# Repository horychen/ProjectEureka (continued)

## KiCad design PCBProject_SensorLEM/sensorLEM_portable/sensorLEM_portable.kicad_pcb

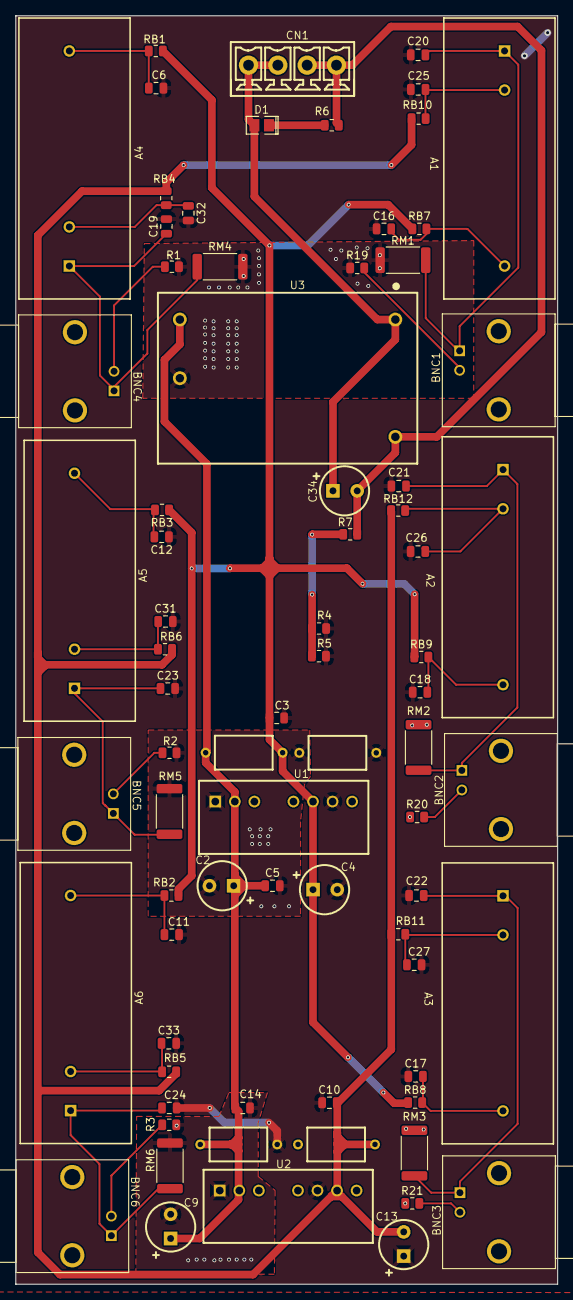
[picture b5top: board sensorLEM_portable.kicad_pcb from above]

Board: 2 copper layers, 70.4 x 164.8 mm, 76 parts (0 on the bottom side), 32 nets.

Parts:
A1, A2, A3, A4, A5, A6: LA55-P; LEM_LA 55-P
BNC1, BNC2, BNC3, BNC4, BNC5, BNC6: BNC; CPBNCPC010
C1, C7, C8, C15: 1nF; CAP-TH_L7.5-W4.5-P10.00-D0.6
C2, C4, C9, C13, C34: 100uf 25V 贴片铝电解; CAP_6.4mm
C3, C5, C10, C14: 105; C_0805_2012Metric
C6, C11, C12, C16, C17, C18, C25, C26, C27, C31, C32, C33: 47nf; C_0805_2012Metric
C19, C20, C21, C22, C23, C24: 4.7uF; C_0805_2012Metric
CN1: DB2EVC-3.81-4P-GN; CONN-TH_4P-P3.81_DB2EVC-3.81-4P
D1: LED0; LED0805
R1, R2, R3, R19, R20, R21: 0R; R_0805_2012Metric
R4, R5, R7: DNP; R_0805_2012Metric
R6: 4.7k; R_0805_2012Metric
RB1, RB2, RB3, RB4, RB5, RB6, RB7, RB8, RB9, RB10, RB11, RB12: 0R; R_0805_2012Metric
RM1, RM2, RM3, RM4, RM5, RM6: 24R 1%精度; R_2512_6332Metric
U1, U2: VRB1212S-6WR3; SIP,22x9.5mm
U3: FT-AX1D; PWRM-TH_MORNSUN_FT-AX1D

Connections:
12VGND: C3.2, C4.2, C6.1, C7.2, C8.2, C10.1, C11.1, C12.1, C13.1, C16.1, C17.1, C18.1, C19.2, C20.2, C21.2, C22.2, C23.2, C24.2, C25.2, C26.2, C27.2, C31.2, C32.2, C33.2, R4.2, R5.2, U1.7 (0V), U2.6 (VO+)
+12: C1.2, C3.1, C4.1, RB1.1, RB2.1, RB3.1, RB7.1, RB8.1, RB9.1, U1.6 (VO+)
-12: C10.2, C13.2, C15.2, RB4.2, RB5.2, RB6.2, RB10.2, RB11.2, RB12.2, U2.7 (0V)
/CSO1: A1.1 (M), BNC1.1 (X), C20.1, RM1.1
/CSO2: A2.1 (M), BNC2.1 (X), C21.1, RM2.1
/CSO3: A3.1 (M), BNC3.1 (X), C22.1, RM3.1
/CSO4: A4.1 (M), BNC4.1 (X), C19.1, RM4.1
/CSO5: A5.1 (M), BNC5.1 (X), C23.1, RM5.1
/CSO6: A6.1 (M), BNC6.1 (X), C24.1, RM6.1
A12V: C1.1, C2.1, C5.1, C8.1, C9.1, C14.1, U1.2 (VIN), U2.2 (VIN), U3.4 (-VO)
AGND: C2.2, C5.2, C7.1, C9.2, C14.2, C15.1, R1.1, R2.1, R3.1, R4.1, R5.1, R7.2, R19.1, R20.1, R21.1, RM1.2, RM2.2, RM3.2, RM4.2, RM5.2, RM6.2, U1.1 (GND), U2.1 (GND), U3.3 (+VO)
D12V1: C34.1, CN1.1, CN1.2, D1.1 (A), U3.1 (-VIN)
D12VGND: C34.2, CN1.3, CN1.4, R6.1, R7.1, U3.2 (+VIN)
unnamed: A1.2 (NEG), C25.1, RB10.1
unnamed: A1.3 (POS), C16.2, RB7.2
unnamed: A2.2 (NEG), C26.1, RB12.1
unnamed: A2.3 (POS), C18.2, RB9.2
unnamed: A3.2 (NEG), C27.1, RB11.1
unnamed: A3.3 (POS), C17.2, RB8.2
unnamed: A4.2 (NEG), C32.1, RB4.1
unnamed: A4.3 (POS), C6.2, RB1.2
unnamed: A5.2 (NEG), C31.1, RB6.1
unnamed: A5.3 (POS), C12.2, RB3.2
unnamed: A6.2 (NEG), C33.1, RB5.1
unnamed: A6.3 (POS), C11.2, RB2.2
unnamed: BNC1.2 (Y), R19.2
unnamed: BNC2.2 (Y), R20.2
unnamed: BNC3.2 (Y), R21.2
unnamed: BNC4.2 (Y), R1.2
unnamed: BNC5.2 (Y), R2.2
unnamed: BNC6.2 (Y), R3.2
unnamed: D1.2 (K), R6.2

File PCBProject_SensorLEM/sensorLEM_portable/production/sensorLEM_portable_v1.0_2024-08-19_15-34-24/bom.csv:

Designator,Footprint,Quantity,Value,LCSC Part #
"A1, A2, A3, A4, A5, A6",LEM_LA 55-P,6,LA55-P,
"BNC1, BNC2, BNC3, BNC4, BNC5, BNC6",CPBNCPC010,6,BNC,
"C1, C15, C7, C8",CAP-TH_L7.5-W4.5-P10.00-D0.6,4,1nF,
"C10, C14, C3, C5",0805,4,105,
"C11, C12, C16, C17, C18, C25, C26, C27, C31, C32, C33, C6",0805,12,47nf,
"C13, C2, C34, C4, C9",CAP_6.4mm,5,100uf 25V 贴片铝电解,
"C19, C20, C21, C22, C23, C24",0805,6,4.7uF,
CN1,CONN-TH_4P-P3.81_DB2EVC-3.81-4P,1,DB2EVC-3.81-4P-GN,
D1,LED0805,1,LED0,
"R1, R19, R2, R20, R21, R3, RB1, RB10, RB11, RB12, RB2, RB3, RB4, RB5, RB6, RB7, RB8, RB9",0805,18,0R,
R6,0805,1,4.7k,
"RM1, RM2, RM3, RM4, RM5, RM6",2512,6,24R 1%精度,
"U1, U2","SIP,22x9.5mm",2,VRB1212S-6WR3,
U3,PWRM-TH_MORNSUN_FT-AX1D,1,FT-AX1D,

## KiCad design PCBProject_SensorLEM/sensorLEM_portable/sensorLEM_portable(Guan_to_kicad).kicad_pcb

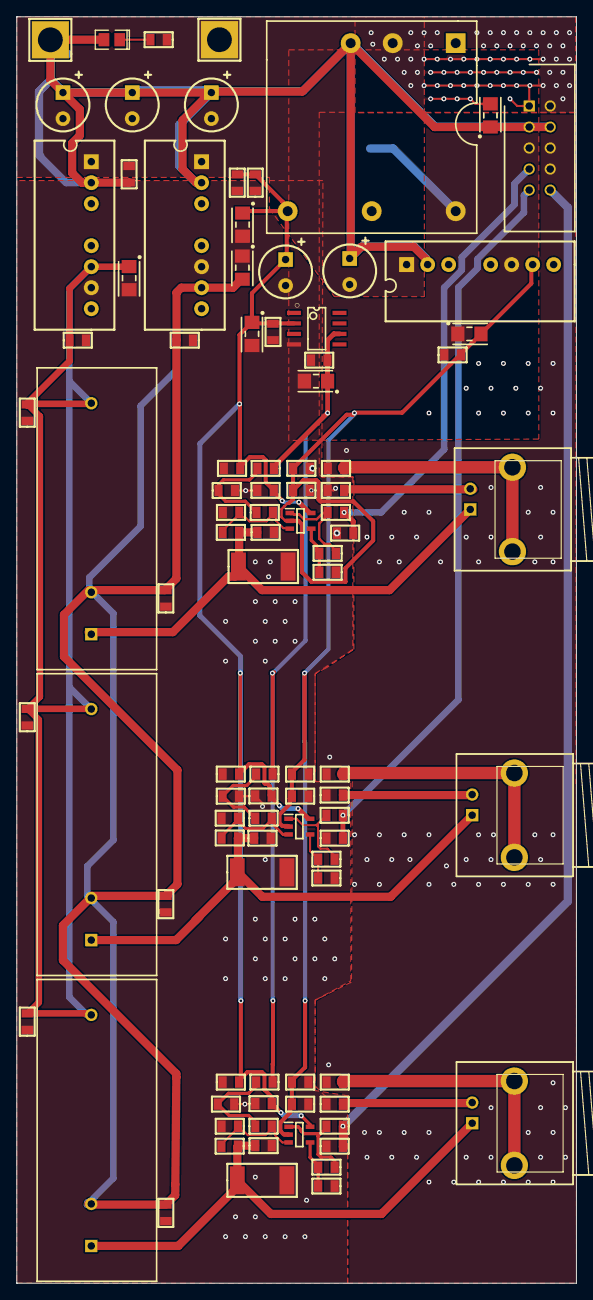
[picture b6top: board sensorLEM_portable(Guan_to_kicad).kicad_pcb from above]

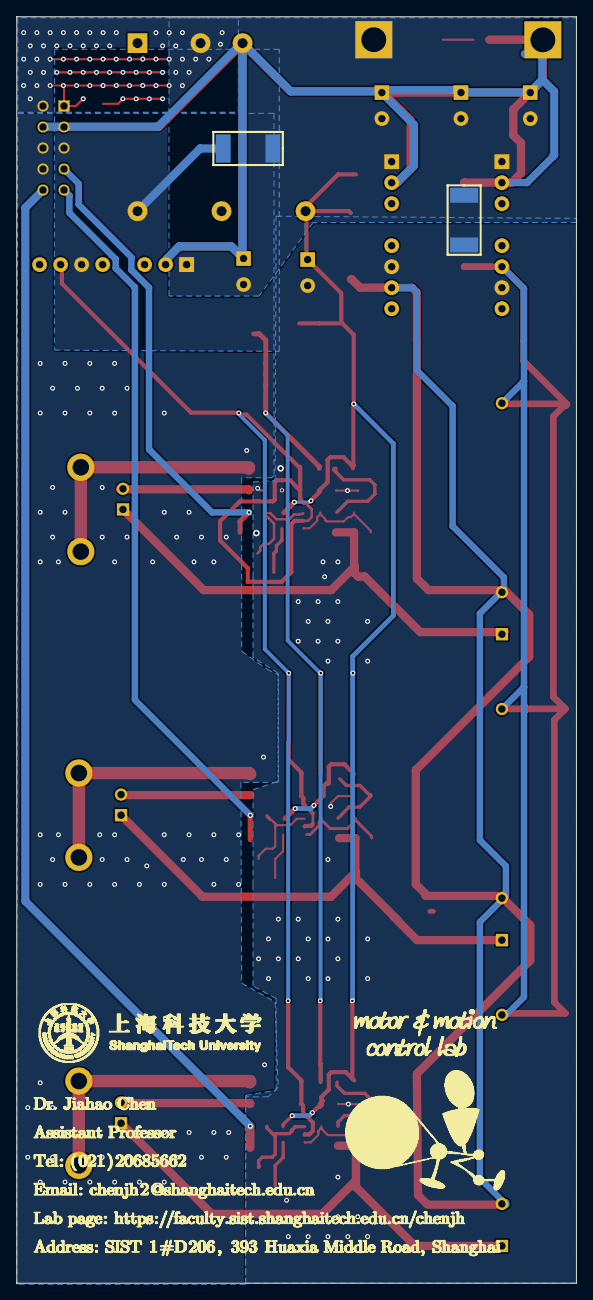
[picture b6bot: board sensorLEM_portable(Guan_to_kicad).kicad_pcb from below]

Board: 2 copper layers, 67.7 x 153.2 mm, 98 parts (2 on the bottom side), 34 nets.

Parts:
A1, A4, A6: LTC6240HV; SOT95P280X100-5N
A2, A3, A5: LA55-P; XDCR_LA55-P
A7, A8: VRB1215S-6WR3; VRB_S-6WR3
BNC1, BNC2, BNC3: BNC
C1, C3, C15, C20, C32, C34, C45: 105; 0805
C2, C5, C16, C46, C60: 100uf 25V 贴片铝电解; CAP/6.4mm -
C4, C8, C17, C47, C51: 22uf 16V; 1206 (钽电容)
C6, C11, C19, C23, C33, C41: 47nf; 0805
C7, C13, C14, C21, C26, C31, C39, C43, C44: 103; 0805
C9, C22, C40: 101; 0805
C10, C12, C18, C24, C37, C38, C42, C48, C49, C54: 104; 0805
C35, C36: 106 25V; 1206 (钽电容)
C52, C55, C56: 102; 0805
D4: LED0; l0805
J1: HIF3FC-10PA-2.54DSA_71_; SHDR10W50P254_2X5_2020X850X920P
J2, J3: Header 2; 接地柱M3
R1, R6, R8, R11, R13, R16: 20k; 0805
R2, R5: DNP; 2512
R3, R7, R9, R12, R14, R17: 10k; 0805
R4, R10, R15: 470R; 0805
R18: 1k; 0805
R19, R20, R21: 0R; 0805
RB1, RB2, RB3: 0R; 0805
RM1, RM2, RM3: 24R 1%精度; 2512
RU1, RU2, RU3: DNP; 0805
U1: URB2405YMD-15W; URB-YMD-15WR3
U2: VRB1205S-6WR3; VRB_S-6WR3
U4: ADR423ARZ; SOIC-8

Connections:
A+5V: A1.5, A4.5, A6.5, C1.2, C3.1, C4.1, C5.1, C7.2, C10.2, C20.2, C21.2, C34.2, C35.1, C37.2, C39.2, U1.4, U4.2
A+15V: A2.3, A3.3, A5.3, A7.6, C6.2, C19.2, C33.2, C47.1, C49.1
A-5V: A1.2, A4.2, A6.2, C14.2, C15.2, C17.2, C18.2, C31.2, C32.2, C44.2, C45.2, U2.7
A-15V: A2.2, A3.2, A5.2, A8.7, C11.2, C23.1, C41.1, C51.2, C54.2
AGND: A7.7, A8.6, C1.1, C3.2, C4.2, C5.2, C6.1, C7.1, C9.2, C10.1, C11.1, C12.2, C13.1, C14.1, C15.1, C17.1, C18.1, C19.1, C20.1, C21.1, C22.2, C23.2, C24.2, C26.1, C31.1, C32.1, C33.1, C34.1, C35.2, C36.2, C37.1, C38.1, C39.1, C40.2, C41.2, C42.2, C43.1, C44.1, C45.1, C47.2, C49.2, C51.1, C54.1, J1.5, R2.2, R5.2, R6.1, R11.1, R16.1, R19.1, R20.1, R21.1, RM1.2, RM2.2, RM3.2, RU1.2, RU2.2, RU3.2, U1.6, U2.6, U4.4
CSO1: A2.1, BNC1.1, C12.1, R3.1, RM1.1
CSO2: A3.1, BNC2.1, C24.1, R9.1, RM2.1
CSO3: A5.1, BNC3.1, C42.1, R14.1, RM3.1
D12V1: A7.2, A8.2, C2.1, C8.1, C16.1, C46.1, C48.2, C60.1, D4.1, J1.3, J1.4, J2.1, U1.3, U2.2
D12VGND: A7.1, A8.1, C2.2, C8.2, C16.2, C46.2, C48.1, C60.2, J1.1, J1.2, J3.1, R2.1, R5.1, R18.1, U1.2, U2.1
NetA1_1: A1.1, R4.2, R7.1
NetA1_3: A1.3, C9.1, R1.2, R3.2
NetA1_4: A1.4, R6.2, R7.2
NetA4_1: A4.1, R10.2, R12.1
NetA4_3: A4.3, C22.1, R8.2, R9.2
NetA4_4: A4.4, R11.2, R12.2
NetA6_1: A6.1, R15.2, R17.1
NetA6_3: A6.3, C40.1, R13.2, R14.2
NetA6_4: A6.4, R16.2, R17.2
NetBNC1_2: BNC1.2, R19.2
NetBNC1_3: BNC1.3, BNC1.4, C52.1
NetBNC2_2: BNC2.2, R20.2
NetBNC2_3: BNC2.3, BNC2.4, C55.1
NetBNC3_2: BNC3.2, R21.2
NetBNC3_3: BNC3.3, BNC3.4, C56.1
NetD4_2: D4.2, R18.2
NetR1_1: R1.1, RB1.2, RU1.1
NetR8_1: R8.1, RB2.2, RU2.1
NetR13_1: R13.1, RB3.2, RU3.1
PE_GND: C52.2, C55.2, C56.2, J1.6, J1.8
REF_3V: C36.1, C38.2, RB1.1, RB2.1, RB3.1, U4.6
VSO1: C13.2, J1.7, R4.1
VSO2: C26.2, J1.9, R10.1
VSO3: C43.2, J1.10, R15.1

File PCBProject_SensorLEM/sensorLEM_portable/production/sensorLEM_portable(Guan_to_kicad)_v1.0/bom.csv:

Designator,Footprint,Quantity,Value,LCSC Part #
"A1, A4, A6",SOT95P280X100-5N,3,LTC6240HV,
"A2, A3, A5",XDCR_LA55-P,3,LA55-P,
"A7, A8",VRB_S-6WR3,2,VRB1215S-6WR3,
"BNC1, BNC2, BNC3",BNC,3,BNC,
"C1, C15, C20, C3, C32, C34, C45",0805,7,105,
"C10, C12, C18, C24, C37, C38, C42, C48, C49, C54",0805,10,104,
"C11, C19, C23, C33, C41, C6",0805,6,47nf,
"C13, C14, C21, C26, C31, C39, C43, C44, C7",0805,9,103,
"C16, C2, C46, C5, C60",CAP/6.4mm -,5,100uf 25V 贴片铝电解,
"C17, C4, C47, C51, C8",1206 (钽电容),5,22uf 16V,
"C22, C40, C9",0805,3,101,
"C35, C36",1206 (钽电容),2,106 25V,
"C52, C55, C56",0805,3,102,
D4,l0805,1,LED0,
J1,SHDR10W50P254_2X5_2020X850X920P,1,HIF3FC-10PA-2.54DSA_71_,
"J2, J3",接地柱M3,2,Header 2,
"R1, R11, R13, R16, R6, R8",0805,6,20k,
"R10, R15, R4",0805,3,470R,
"R12, R14, R17, R3, R7, R9",0805,6,10k,
R18,0805,1,1k,
"R19, R20, R21, RB1, RB2, RB3",0805,6,0R,
"RM1, RM2, RM3",2512,3,24R 1%精度,
U1,URB-YMD-15WR3,1,URB2405YMD-15W,
U2,VRB_S-6WR3,1,VRB1205S-6WR3,
U4,SOIC-8,1,ADR423ARZ,

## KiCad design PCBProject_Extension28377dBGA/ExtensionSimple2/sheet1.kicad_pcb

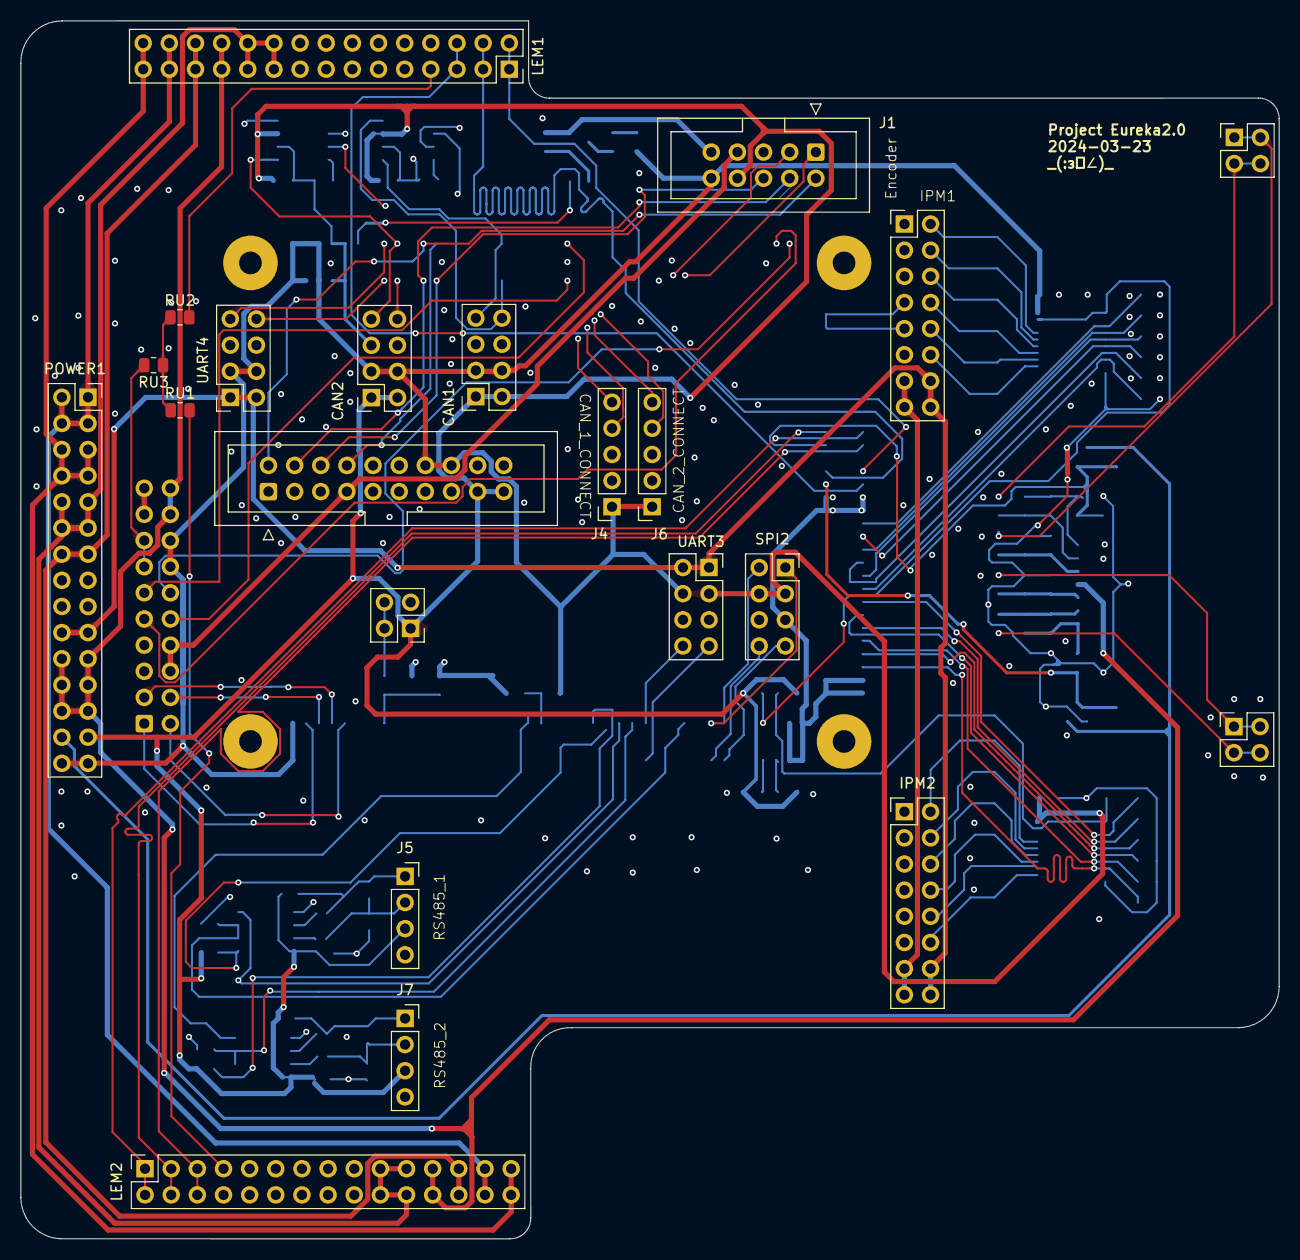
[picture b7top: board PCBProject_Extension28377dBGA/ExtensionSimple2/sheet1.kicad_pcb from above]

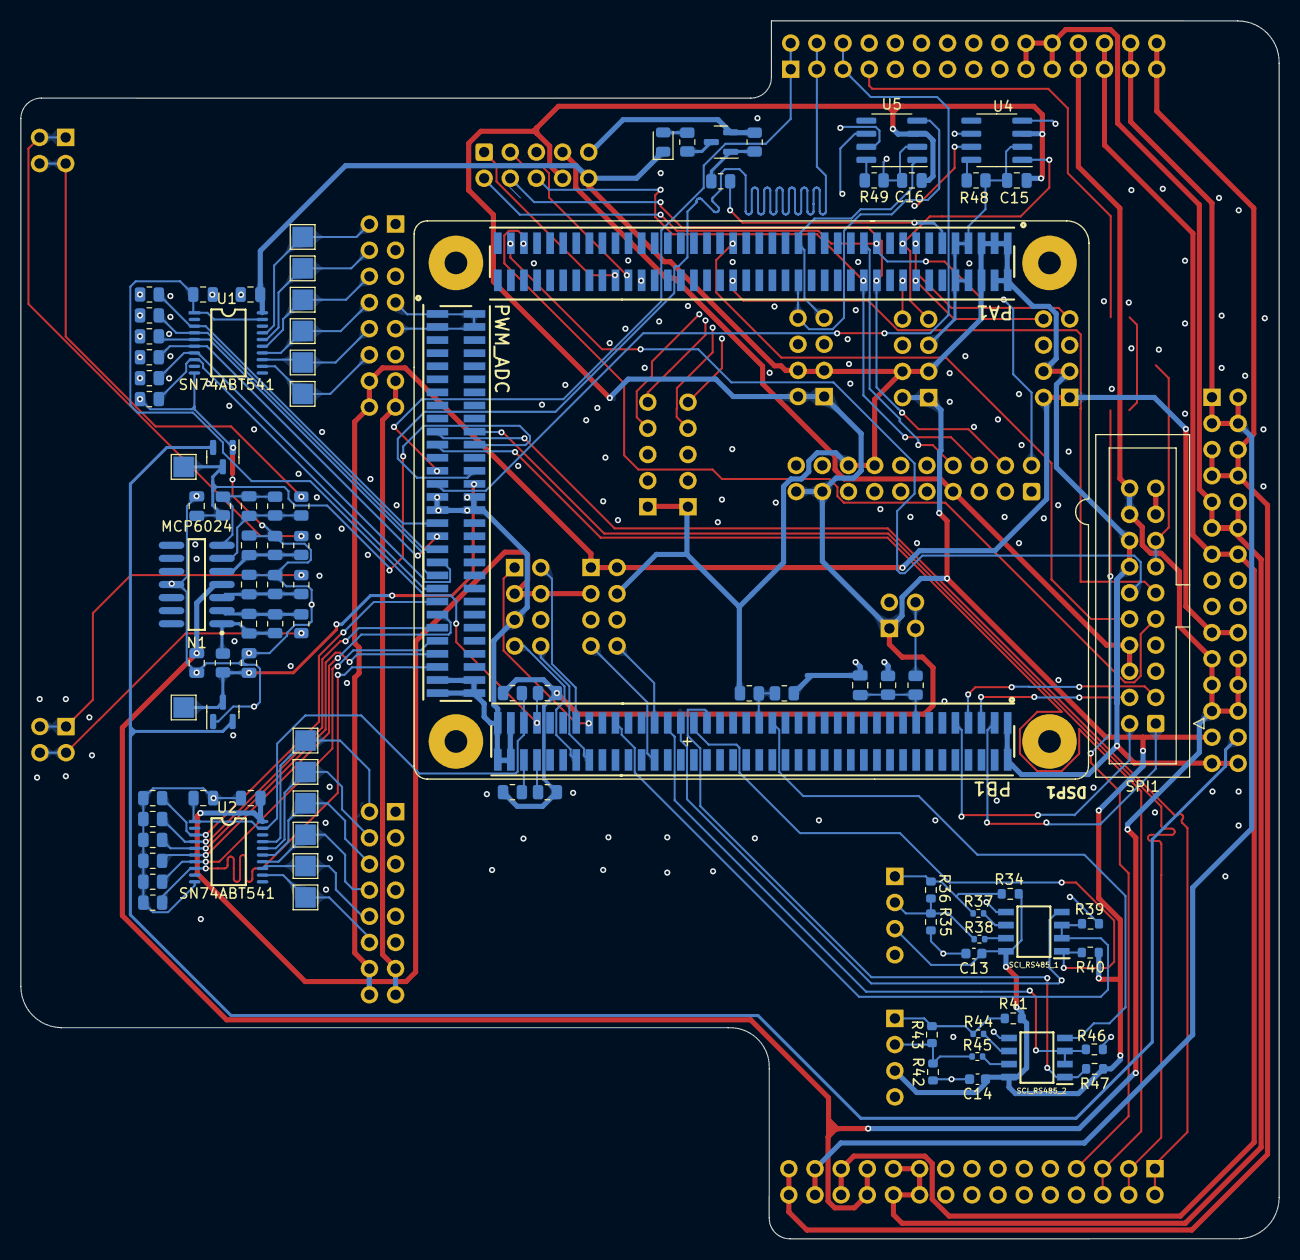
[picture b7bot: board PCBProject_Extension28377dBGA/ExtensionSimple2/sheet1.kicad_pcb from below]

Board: 4 copper layers, 122.2 x 118.3 mm, 114 parts (92 on the bottom side), 117 nets.

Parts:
C1, C2, C3, C4, C9, C15, C16: 104; C_0805_2012Metric
C5, C6, C7, C8: 102; C_0805_2012Metric
C10, C11, C12: 103; C_0805_2012Metric
C13, C14: 0.1uF; C_0603_1608Metric
CAN1, CAN2: Conn_02x04_Counter_Clockwise; PinSocket_2x04_P2.54mm_Vertical
D1, D2: BAR43S; SOT-23
D3: LEDRED; LED_0805_2012Metric
DI1: Conn_02x02_Counter_Clockwise; PinSocket_2x02_P2.54mm_Vertical
DSP1: DSP_240_SMD
INC1: HIF3FC-20PA-2.54DSA; IDC-Header_2x10_P2.54mm_Vertical
IPM1, IPM2: Conn_02x08_Top_Bottom; PinSocket_2x08_P2.54mm_Vertical
J1: Conn_02x05_Odd_Even; IDC-Header_2x05_P2.54mm_Vertical
J2, J3: Conn_01x02_Pin; PinSocket_2x02_P2.54mm_Vertical
J4: CAN_1_CONNECT; PinSocket_1x05_P2.54mm_Vertical
J5: RS485_1_CONNECT; PinSocket_1x04_P2.54mm_Vertical
J6: CAN_2_CONNECT; PinSocket_1x05_P2.54mm_Vertical
J7: RS485_2_CONNECT; PinSocket_1x04_P2.54mm_Vertical
LEM1, LEM2: HIF3FC-30PA-2.54DSA; PinSocket_2x15_P2.54mm_Vertical
N1: MCP6024; SOIC14_M
POWER1: HIF3FC-30PA-2.54DSA; PinSocket_2x15_P2.54mm_Vertical
Q1: FMMT618TA; SOT-23
R1, R2, R3, R4, R7, R8, R9, R10, R11, R12, R48, R49: 4.7k; R_0805_2012Metric
R5, R6: 4.7K; R_0805_2012Metric
R13, R14, R15, R16: 0R; R_0805_2012Metric
R17, R18, R19, R20, R27, R28, R29, R32, R33: 10K; R_0805_2012Metric
R21, R22, R24, R31: 1K; R_0805_2012Metric
R23: 100R; R_0805_2012Metric
R25: 1.69K/1%; R_0805_2012Metric
R26: 3.3K/1%; R_0805_2012Metric
R30: 2K; R_0805_2012Metric
R34, R35, R39, R40, R41, R42, R46, R47: 10K; R_0603_1608Metric
R36, R43: 120R; R_0603_1608Metric
R37, R38, R44, R45: 10R; R_0402_1005Metric
RU1, RU2: DNP; R_0805_2012Metric
RU3: 0R; R_0805_2012Metric
SCI_RS485_1, SCI_RS485_2: SN65HVD75D; SOIC127P600X175-8N
SPI1: HIF3FC-20PA-2.54DSA; IDC-Header_2x10_P2.54mm_Vertical
SPI2: Conn_02x04_Counter_Clockwise; PinSocket_2x04_P2.54mm_Vertical
TP1, TP2, TP3, TP4, TP5, TP6, TP7, TP8, TP9, TP10, TP11, TP12: TP-黄色测试点; TestPoint_Pad_2.0x2.0mm
U1, U2: SN74ABT541; TSSOP-20
U4, U5: SN65HVD230; SOIC-8_3.9x4.9mm_P1.27mm
UART3, UART4: Conn_02x04_Counter_Clockwise; PinSocket_2x04_P2.54mm_Vertical
VDC_BUS1, VDC_BUS2: TP-黄色测试点; TestPoint_Pad_2.0x2.0mm

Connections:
12VGND: LEM1.19, LEM1.20, LEM1.21, LEM1.22, LEM2.19, LEM2.20, LEM2.21, LEM2.22, POWER1.9, POWER1.10, POWER1.11, POWER1.12
+12: LEM1.27, LEM1.28, LEM2.27, LEM2.28, POWER1.1, POWER1.2, POWER1.3, POWER1.4
-5V_ADC: SPI1.17, SPI1.19
-12: LEM1.29, LEM1.30, LEM2.29, LEM2.30, POWER1.5, POWER1.6, POWER1.7, POWER1.8
/BootFromFlash: DSP1.119 (119_GP84), R25.1, R26.2
/CAN_1H: J4.4, U4.7 (CANH)
/CAN_1L: J4.5, U4.6 (CANL)
/CAN_2H: J6.4, U5.7 (CANH)
/CAN_2L: J6.5, U5.6 (CANL)
/DC_BUS_2M1: J2.1, J2.3, R14.2
/DC_BUS_2M2: J3.1, J3.3, R16.2
/DI-1-DSP-3.3V: C12.2, DSP1.95 (95_D9), R23.1, R24.1
/DSP-PWM1A: DSP1.193 (193_PWM1A), R1.2, U1.3 (A2)
/DSP-PWM1B: DSP1.195 (195_PWM1B), R7.2, U1.6 (A5)
/DSP-PWM2A: DSP1.197 (197_PWM2A), R3.2, U1.4 (A3)
/DSP-PWM2B: DSP1.199 (199_PWM2B), R9.2, U1.7 (A6)
/DSP-PWM3A: DSP1.201 (201_PWM3A), R5.2, U1.5 (A4)
/DSP-PWM3B: DSP1.203 (203_PWM3B), R11.2, U1.8 (A7)
/DSP-PWM4A: DSP1.205 (205_PWM4A), R2.2, U2.3 (A2)
/DSP-PWM4B: DSP1.207 (207_PWM4B), R8.2, U2.6 (A5)
/DSP-PWM5A: DSP1.209 (209_PWM5A), R4.2, U2.4 (A3)
/DSP-PWM5B: DSP1.211 (211_PWM5B), R10.2, U2.7 (A6)
/DSP-PWM6A: DSP1.213 (213_PWM6A), R6.2, U2.5 (A4)
/DSP-PWM6B: DSP1.215 (215_PWM6B), R12.2, U2.8 (A7)
/DSP_A_CAN_RX: CAN2.8, DSP1.18 (GP62_18), U4.4 (R)
/DSP_A_CAN_TX: CAN2.7, DSP1.17 (17_GP19), U4.1 (D)
/DSP_B_CAN_RX: CAN1.8, DSP1.34 (GP21_34), U5.4 (R)
/DSP_B_CAN_TX: CAN1.7, DSP1.33 (33_GP20), U5.1 (D)
/DSP_PWM1~_ENABLE: C1.2, DSP1.153 (153_GP108), R27.1, U1.1 (*OE1), U1.19 (*OE2)
/DSP_PWM2~_ENABLE: C2.2, DSP1.155 (155_GP93), R28.1, U2.1 (*OE1), U2.19 (*OE2)
/DSP_PWM3~_ENABLE: DSP1.154 (GP28_154), R32.2
/DSP_PWM4~_ENABLE: DSP1.156 (GP29_156), R33.2
/GND_2M1: J2.2, J2.4, R13.2
/GND_2M2: J3.2, J3.4, R15.2
/IPM_IU1: DSP1.187 (187_ADA1), LEM1.5, LEM1.6
/IPM_IU2: DSP1.181 (181_ADB1), LEM2.5, LEM2.6
/IPM_IV1: DSP1.186 (ADA2_186), LEM1.3, LEM1.4
/IPM_IV2: DSP1.180 (ADB2_180), LEM2.3, LEM2.4
/IPM_IW1: DSP1.185 (185_ADA3), LEM1.1, LEM1.2
/IPM_IW2: DSP1.179 (179_ADB3), LEM2.1, LEM2.2
/IPM_VDC_BUS1: C10.2, D1.3, DSP1.188 (ADA0_188), R21.2, VDC_BUS1.1
/IPM_VDC_BUS2: C11.2, D2.3, DSP1.182 (ADB0_182), R22.2, VDC_BUS2.1
/LED1: DSP1.11 (11_GP3), R29.2
/MQEP1A: DSP1.21 (21_GP96), INC1.2, J1.2
/MQEP1B: DSP1.22 (GP97_22), INC1.4, J1.4
/MQEP1S: DSP1.23 (23_GP98), INC1.8
/MQEP1Z: DSP1.24 (GP99_24), INC1.6, J1.6
/PWM1A_5V: IPM1.2, TP11.1, U1.17 (Y2)
/PWM1B_5V: IPM1.8, TP5.1, U1.14 (Y5)
/PWM2A_5V: IPM1.4, TP9.1, U1.16 (Y3)
/PWM2B_5V: IPM1.10, TP3.1, U1.13 (Y6)
/PWM3A_5V: IPM1.6, TP7.1, U1.15 (Y4)
/PWM3B_5V: IPM1.12, TP1.1, U1.12 (Y7)
/PWM4A_5V: IPM2.2, TP12.1, U2.17 (Y2)
/PWM4B_5V: IPM2.8, TP6.1, U2.14 (Y5)
/PWM5A_5V: IPM2.4, TP10.1, U2.16 (Y3)
/PWM5B_5V: IPM2.10, TP4.1, U2.13 (Y6)
/PWM6A_5V: IPM2.6, TP8.1, U2.15 (Y4)
/PWM6B_5V: IPM2.12, TP2.1, U2.12 (Y7)
/QEP1_HALL_U: DSP1.62 (GP68_62), INC1.1, J1.1
/QEP1_HALL_V: DSP1.60 (GP94_60), INC1.3, J1.3
/QEP1_HALL_W: DSP1.58 (GP17_58), INC1.5, J1.5
/RS485_1_A: J5.1, R34.1, R36.2, R37.1
/RS485_1_B: J5.2, R35.2, R36.1, R38.1
/RS485_2_A: J7.1, R41.1, R43.2, R44.1
/RS485_2_B: J7.2, R42.2, R43.1, R45.1
/SPI B MI HS: DSP1.147 (147_GP64), SPI2.2
/SPI B MO HS: DSP1.145 (145_GP63), SPI2.1
/SPI_A_CK_HS: DSP1.44 (GP60_44), SPI1.11
/SPI_A_MI_HS: DSP1.77 (77_GP59), SPI1.12
/SPI_A_MO_HS: DSP1.75 (75_GP58), SPI1.9
/SPI_B_CK_HS: DSP1.146 (GP65_146), SPI2.8
/SPI_C_CK_HS: DSP1.87 (87_D13), SPI1.3
/SPI_C_MI_HS: DSP1.85 (85_D14), SPI1.4
/SPI_C_MO_HS: DSP1.83 (83_D15), SPI1.1
/UART_SCI_RXDA: DSP1.129 (129_GP136), R40.2, SCI_RS485_1.1 (R)
/UART_SCI_RXDB: DSP1.127 (127_GP138), R47.2, SCI_RS485_2.1 (R)
/UART_SCI_RXDC: DSP1.135 (135_GP139), UART3.8
/UART_SCI_RXDD: DSP1.15 (15_GP141), UART4.7
/UART_SCI_TXDA: DSP1.131 (131_GP135), SCI_RS485_1.4 (D)
/UART_SCI_TXDB: DSP1.117 (117_GP137), SCI_RS485_2.4 (D)
/UART_SCI_TXDC: DSP1.136 (GP140_136), UART3.7
/UART_SCI_TXDD: DSP1.16 (GP142_16), UART4.8
/UART_WRA: DSP1.141 (141_GP132), R39.2, SCI_RS485_1.2 (RE), SCI_RS485_1.3 (DE)
/UART_WRB: DSP1.133 (133_GP134), R46.2, SCI_RS485_2.2 (RE), SCI_RS485_2.3 (DE)
/~SPI_A_STE_HS: DSP1.43 (43_GP61), SPI1.10
/~SPI_B_STE_HS: DSP1.148 (GP143_148), SPI2.7
/~SPI_C_STE_HS: DSP1.89 (89_D12), SPI1.2
A+5V: C9.2, LEM1.23, LEM1.24, LEM2.23, LEM2.24, N1.4, POWER1.21, POWER1.22, POWER1.23, POWER1.24, POWER1.25, POWER1.26, SPI1.18, SPI1.20
A-5V: LEM1.25, LEM1.26, LEM2.25, LEM2.26, POWER1.13, POWER1.14
AGND: C1.1, C2.1, C3.2, C4.2, C5.1, C6.1, C9.1, C10.1, C11.1, C12.1, C13.2, C14.2, C15.2, C16.2, CAN1.5, CAN1.6, CAN2.5, CAN2.6, D1.1, D2.1, DI1.2, DSP1.7 (7_GND), DSP1.8 (GND_8), DSP1.9 (9_GND), DSP1.10 (GND10), DSP1.157 (157_GND), DSP1.158 (GND_158), DSP1.159 (159_GND), DSP1.160 (GND_160), DSP1.161 (161_GND), DSP1.162 (GND_162), DSP1.163 (163_GND), DSP1.164 (GND_164), DSP1.189 (189_GND), DSP1.190 (GND_190), DSP1.191 (191_GND), DSP1.192 (GND_192), DSP1.217 (217_GND), DSP1.218 (GND_218), DSP1.219 (219_GND), DSP1.220 (GND_220), INC1.9, INC1.10, INC1.11, INC1.12, INC1.13, IPM1.1, IPM1.3, IPM1.5, IPM1.7, IPM1.9, IPM1.11, IPM2.1, IPM2.3, IPM2.5, IPM2.7, IPM2.9, IPM2.11, J1.9, J4.2, J5.4, J6.2, J7.4, LEM1.8, LEM1.9, LEM1.10, LEM1.11, LEM1.12, LEM1.13, LEM1.14, LEM1.15, LEM1.16, LEM1.17, LEM1.18, LEM2.8, LEM2.9, LEM2.10, LEM2.11, LEM2.12, LEM2.13, LEM2.14, LEM2.15, LEM2.16, LEM2.17, LEM2.18, N1.11, POWER1.15, POWER1.16, POWER1.17, POWER1.18, Q1.2 (E), R1.1, R2.1, R3.1, R4.1, R5.1, R6.1, R7.1, R8.1, R9.1, R10.1, R11.1, R12.1, R17.1, R18.1, R24.2, R26.1, R30.2, R35.1, R39.1, R42.1, R46.1, R48.2, R49.2, SCI_RS485_1.5 (GND), SCI_RS485_2.5 (GND), SPI1.5, SPI1.7, SPI2.5, SPI2.6, U1.10 (GND), U2.10 (GND), U4.2 (GND), U5.2 (GND), UART3.5, UART3.6, UART4.5, UART4.6
AVDD: D1.2, D2.2, POWER1.28
D12V1: IPM1.14, IPM1.16, IPM2.14, IPM2.16, POWER1.19, POWER1.20, UART3.1, UART3.2, UART4.1, UART4.2
D12VGND: IPM1.13, IPM1.15, IPM2.13, IPM2.15
D+5V: C3.1, C4.1, CAN1.3, CAN1.4, CAN2.3, CAN2.4, D3.1 (A), DSP1.1 (1_+5V), DSP1.2 (+5V_2), DSP1.3 (3_+5V), DSP1.4 (+5V_4), DSP1.5 (5_+5V), DSP1.6 (+5V_6), DSP1.81 (81+5V), DSP1.82 (+5V_82), INC1.14, INC1.16, J1.10, J4.1, J6.1, POWER1.29, POWER1.30, R25.2, SPI1.14, SPI1.16, SPI2.3, SPI2.4, U1.20 (VCC), U2.20 (VCC), UART3.3, UART3.4, UART4.3, UART4.4
unnamed: C5.2, N1.3, R14.1, R17.2
unnamed: C6.2, N1.5, R16.1, R18.2
unnamed: C7.1, N1.2, R13.1, R19.1
unnamed: C7.2, N1.1, R19.2, R21.1
unnamed: C8.1, N1.6, R15.1, R20.1
unnamed: C8.2, N1.7, R20.2, R22.1
unnamed: D3.2 (K), R31.2
unnamed: DI1.3, DI1.4, R23.2
unnamed: LEM1.7, RU2.2
unnamed: LEM2.7, RU1.2
unnamed: Q1.1 (B), R29.1, R30.1
unnamed: Q1.3 (C), R31.1
unnamed: RU3.2, SPI1.13, SPI1.15
unnamed: R37.2, SCI_RS485_1.6 (A)
unnamed: R38.2, SCI_RS485_1.7 (B)
unnamed: R44.2, SCI_RS485_2.6 (A)
unnamed: R45.2, SCI_RS485_2.7 (B)
unnamed: R48.1, U4.8 (Rs)
unnamed: R49.1, U5.8 (Rs)
PE_GND: INC1.7, J1.7, SPI1.6, SPI1.8
REF_3V: RU1.1, RU2.1, RU3.1
VDD: C13.1, C14.1, C15.1, C16.1, CAN1.1, CAN1.2, CAN2.1, CAN2.2, DI1.1, INC1.17, INC1.19, J1.8, J5.3, J7.3, POWER1.27, R27.2, R28.2, R32.1, R33.1, R34.2, R40.1, R41.2, R47.1, SCI_RS485_1.8 (VCC), SCI_RS485_2.8 (VCC), U4.3 (VCC), U5.3 (VCC)

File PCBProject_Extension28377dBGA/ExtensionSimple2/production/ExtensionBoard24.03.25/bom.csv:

Designator,Footprint,Quantity,Value,LCSC Part #
"C1, C15, C16, C2, C3, C4, C9",0805,7,104,
"C10, C11, C12",0805,3,103,
"C13, C14",0603,2,0.1uF,
"C5, C6, C7, C8",0805,4,102,
"CAN1, CAN2, SPI2, UART3, UART4",PinSocket_2x04_P2.54mm_Vertical,5,Conn_02x04_Counter_Clockwise,
"D1, D2",SOT-23,2,BAR43S,
D3,0805,1,LEDRED,
DI1,PinSocket_2x02_P2.54mm_Vertical,1,Conn_02x02_Counter_Clockwise,
DSP1,DSP_240_SMD,1,~,
"INC1, SPI1",IDC-Header_2x10_P2.54mm_Vertical,2,HIF3FC-20PA-2.54DSA,
"IPM1, IPM2",PinSocket_2x08_P2.54mm_Vertical,2,Conn_02x08_Top_Bottom,
J1,IDC-Header_2x05_P2.54mm_Vertical,1,Conn_02x05_Odd_Even,
"J2, J3",PinSocket_2x02_P2.54mm_Vertical,2,Conn_01x02_Pin,
J4,PinSocket_1x05_P2.54mm_Vertical,1,CAN_1_CONNECT,
J5,PinSocket_1x04_P2.54mm_Vertical,1,RS485_1_CONNECT,
J6,PinSocket_1x05_P2.54mm_Vertical,1,CAN_2_CONNECT,
J7,PinSocket_1x04_P2.54mm_Vertical,1,RS485_2_CONNECT,
"LEM1, LEM2, POWER1",PinSocket_2x15_P2.54mm_Vertical,3,HIF3FC-30PA-2.54DSA,
N1,SOIC14_M,1,MCP6024,
Q1,SOT-23,1,FMMT618TA,
"R1, R10, R11, R12, R2, R3, R4, R48, R49, R5, R6, R7, R8, R9",0805,14,4.7k,
"R13, R14, R15, R16, RU3",0805,5,0R,
"R17, R18, R19, R20, R27, R28, R29, R32, R33",0805,9,10K,
"R21, R22, R24, R31",0805,4,1K,
R23,0805,1,100R,
R25,0805,1,1.69K/1%,
R26,0805,1,3.3K/1%,
R30,0805,1,2K,
"R34, R35, R39, R40, R41, R42, R46, R47",0603,8,10K,
"R36, R43",0603,2,120R,
"R37, R38, R44, R45",0402,4,10R,
"SCI_RS485_1, SCI_RS485_2",SOIC127P600X175-8N,2,SN65HVD75D,
"TP1, TP10, TP11, TP12, TP2, TP3, TP4, TP5, TP6, TP7, TP8, TP9, VDC_BUS1, VDC_BUS2",TestPoint_Pad_2.0x2.0mm,14,TP-黄色测试点,
"U1, U2",TSSOP-20,2,SN74ABT541,
"U4, U5",SOIC-8_3.9x4.9mm_P1.27mm,2,SN65HVD230,
